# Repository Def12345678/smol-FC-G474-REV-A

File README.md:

# smol-FC

**Work in progress.** This is a Betaflight-based flight controller project, currently in the hardware design phase. 
Everything can change, it's not a final product. 

## License
This project is licensed under the **CERN Open Hardware Licence v2 - Weakly Reciprocal (CERN-OHL-W-v2)**.

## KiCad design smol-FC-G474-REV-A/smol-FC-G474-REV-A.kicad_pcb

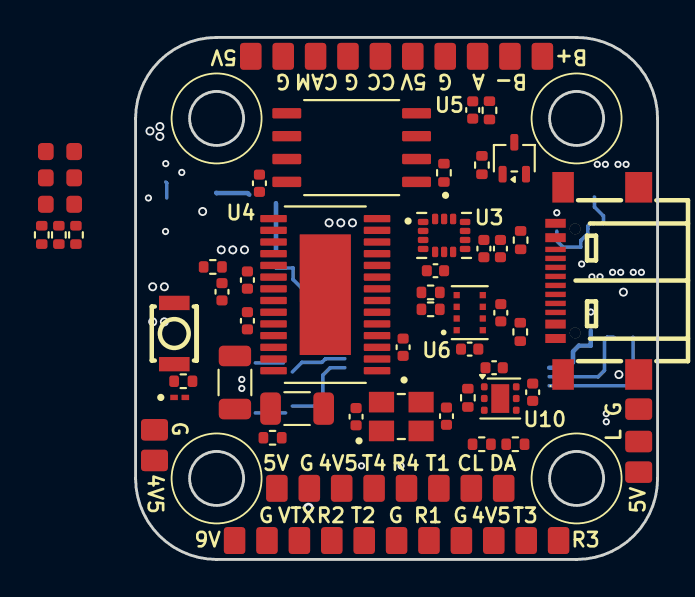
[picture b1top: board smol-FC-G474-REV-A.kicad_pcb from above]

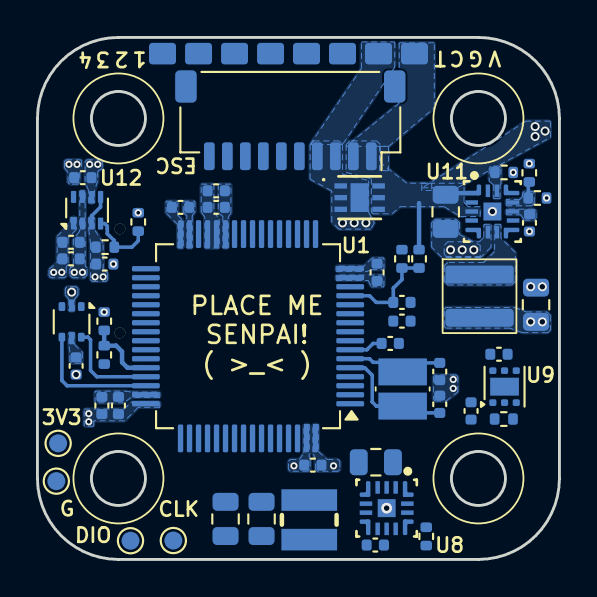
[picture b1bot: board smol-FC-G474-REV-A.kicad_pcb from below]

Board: 6 copper layers, 29.0 x 29.0 mm, 140 parts (60 on the bottom side), 83 nets.

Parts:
3V3: TestPoint; TestPoint_Pad_D1.0mm
4V5, 4V5#2, 4V5#3, 5V, 5V#2, 5V#3, 5V#4, 9V: TestPoint; pad-1.2x1.5
A: TestPoint; pad-1.2x1.5
B+: TestPoint; pad-1.2x1.5
B-: TestPoint; pad-1.2x1.5
C1, C2, C3, C4, C7, C8, C9, C10, C11, C14, C15, C16, C18, C20, C25, C26, C27: 100n; C_0402_1005Metric
C5, C28: 4.7u; C_0402_1005Metric
C6, C33, C34, C36, C39: 1u; C_0402_1005Metric
C12, C13, C23, C24: 10p; C_0402_1005Metric
C17: 2.2u; C_0402_1005Metric
C19: 10n; C_0402_1005Metric
C21, C22: 47u; C_1206_3216Metric
C29, C37: 3.3u; C_0805_2012Metric
C30, C31: 47u; C_0805_2012Metric
C32, C35, C40, C41, C42, C43: 10u; C_0402_1005Metric
C38: 22u; C_0805_2012Metric
CAM: TestPoint; pad-1.2x1.5
CC: TestPoint; pad-1.2x1.5
CL: TestPoint; pad-1.2x1.5
CLK: TestPoint; TestPoint_Pad_D1.0mm
CURR1: TestPoint; pad-1.2x1.5
D1, D2: LED; LED_0603_1608Metric
D3: ESD; DIODE_ESDALC6V1-1U2
D4: RED; LED_0603_1608Metric
DA: TestPoint; pad-1.2x1.5
DIO: TestPoint; TestPoint_Pad_D1.0mm
ESC: ESC; JST_SH_SM10B-SRSS-TB_1x10-1MP_P1.00mm_Horizontal
G: TestPoint; pad-1.2x1.5
G#2, G#3, G#4, G#5, G#6, G#7, G#8, G#9: TestPoint; pad-1.2x1.5
G#10: TestPoint; TestPoint_Pad_D1.0mm
GND4: TestPoint; pad-1.2x1.5
L: TestPoint; pad-1.2x1.5
L1: 1.5u; IND-SMD_L3.0-W3.0_YSMC0320H
L2: 3.3u; APH0430C-3R3M-TCD5
M1, M2, M3, M4: TestPoint; pad-1.2x1.5
Q1: BC817W; SOT-323_SC-70
R1, R2, R8, R19: 1k; R_0402_1005Metric
R1#2, R2#2, R3, R4: TestPoint; pad-1.2x1.5
R3#2, R6, R7, R25: 100k; R_0402_1005Metric
R4#2, R5, R20, R22, R24, R26: 10k; R_0402_1005Metric
R9, R10: 5.1k; R_0402_1005Metric
R11, R12: 75; R_0402_1005Metric
R13: 10K; R_0402_1005Metric
R14, R15, R17, R18: 4.7k; R_0402_1005Metric
R16: 330; R_0402_1005Metric
R21: 7.15k; R_0402_1005Metric
R23: 80.6k; R_0402_1005Metric
R27: 39k; R_0402_1005Metric
SW1: BOOT; KEY-SMD_B3U-1000PM
T1, T2, T3, T4: TestPoint; pad-1.2x1.5
TEL1: TestPoint; pad-1.2x1.5
U1: STM32G474RETx; LQFP-64_10x10mm_P0.5mm
U2: USBLC6-2P6; SOT-666
U3: ICM-42688-P; PQFN50P300X250X97-14N
U4: AT7456E; SOP65P637X110-28N
U5: W25Q128JVSIQ; SOIC127P790X216-8N
U6: DPS368XTSA1; XDCR_DPS368XTSA1
U7: TVS3300DRVR; DRV6_1X1P6_TEX
U8, U11: LMQ66430R5RXBR; RXB0014A-MFG
U9, U10: LP5912-3.3DRV; WSON-6-1EP_2x2mm_P0.65mm_EP1x1.6mm
U12: TPS2116DRL; SOT-583-8
USB1: TYPE-C 16P QTWT; USB-TYPE-C-SMD_TYPE-C-16P-QTWT
VBAT1: TestPoint; pad-1.2x1.5
VTX: TestPoint; pad-1.2x1.5
Y1: 8MHz; XTAL_NX3225GD-8MHZ-STD-CRA-3
Y2: 27MHz; XTAL_TSX-3225_16.0000MF18X-AC3

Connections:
+3V3_CORE: 3V3.1 (1_1), C1.1, C2.1, C3.1, C4.1, C5.1, C6.1, C7.1, C25.1, C33.1, R1.1, R2.1, R8.1, R13.1, R17.1, R18.1, R20.1, SW1.2, U1.1 (VBAT), U1.16 (VDD), U1.28 (VREF+), U1.29 (VDDA), U1.32 (VDD), U1.48 (VDD), U1.64 (VDD), U5.3 (/WP(IO2)), U5.7 (/HOLD/RESET(IO3)), U5.8 (VCC), U9.1 (OUT)
+3V3_SENS: C17.1, C18.1, C19.1, C26.1, C27.1, C36.1, R14.1, R15.1, R22.1, U3.5 (VDDIO), U3.8 (VDD), U6.6 (VDDIO), U6.8 (VDD), U10.1 (OUT)
+5V_BEC: 5V.1 (1_1), 5V#2.1 (1_1), 5V#3.1 (1_1), 5V#4.1 (1_1), C30.1, C31.1, C42.1, L1.2, R25.1, U8.11 (VOUT_FB), U12.3 (VIN1), U12.5 (MODE)
+5V_SYS: 4V5.1 (1_1), 4V5#2.1 (1_1), 4V5#3.1 (1_1), B+.1 (1_1), C14.1, C15.1, C16.1, C32.1, C35.1, C40.1, C41.1, U4.3 (DVDD), U4.19 (~RESET), U4.21 (AVDD), U4.24 (PVDD), U9.4 (EN), U9.6 (IN), U10.4 (EN), U10.6 (IN), U12.2 (VOUT), U12.7 (VOUT)
+9V_BEC: 9V.1 (1_1), C38.1, L2.2, R23.1
+VBAT: C29.1, C37.1, ESC.1, ESC.2, R3#2.1, U7.4 (IN), U7.5 (IN), U7.6 (IN), U8.1 (EN), U8.3 (VIN), U11.1 (EN), U11.3 (VIN), VBAT1.1 (1_1)
+VBUS: C11.1, C43.1, R6.1, U2.5 (VBUS), U12.6 (VIN2), USB1.A4 (VBUS), USB1.A9 (VBUS)
/Connectors/AUX: A.1 (1_1), U1.26 (PB2)
/Connectors/BZ-: B-.1 (1_1), Q1.3 (C)
/Connectors/BZ_G: Q1.1 (B), R19.2
/Connectors/Buzzer: R19.1, U1.43 (PA9)
/Connectors/CC: R16.1, U1.62 (PB9)
/Connectors/CC_P: C28.1, CC.1 (1_1), R16.2
/Connectors/I2C3_SCL: CL.1 (1_1), R17.2, U1.42 (PA8)
/Connectors/I2C3_SDA: DA.1 (1_1), R18.2, U1.41 (PC9)
/Connectors/LED: L.1 (1_1), U1.25 (PB1)
/Connectors/M1: ESC.7, M1.1 (1_1), U1.8 (PC0)
/Connectors/M2: ESC.8, M2.1 (1_1), U1.9 (PC1)
/Connectors/M3: ESC.9, M3.1 (1_1), U1.10 (PC2)
/Connectors/M4: ESC.10, M4.1 (1_1), U1.11 (PC3)
/Connectors/RX1: R1#2.1 (1_1), U1.60 (PB7)
/Connectors/RX2 (VTX): R2#2.1 (1_1), U1.17 (PA3)
/Connectors/RX3 (ELRS): R3.1 (1_1), U1.33 (PB11)
/Connectors/RX4 (GPS): R4.1 (1_1), U1.53 (PC11)
/Connectors/RX5 (TEL): ESC.6, TEL1.1 (1_1), U1.55 (PD2)
/Connectors/TX1: T1.1 (1_1), U1.59 (PB6)
/Connectors/TX2 (VTX): T2.1 (1_1), U1.14 (PA2)
/Connectors/TX3 (ELRS): T3.1 (1_1), U1.30 (PB10)
/Connectors/TX4 (GPS): T4.1 (1_1), U1.52 (PC10)
/Connectors/VIDEO_IN: C20.1, CAM.1 (1_1), R11.1
/Connectors/VIDEO_OUT: R12.2, VTX.1 (1_1)
/MCU/ADC_CURR: C10.1, CURR1.1 (1_1), ESC.5, U1.12 (PA0)
/MCU/ADC_VBAT: C9.1, R3#2.2, R4#2.1, U1.13 (PA1)
/MCU/BOOT: D3.1, R5.1, SW1.1, U1.61 (PB8)
/MCU/HSE_IN: C12.1, U1.5 (PF0), Y1.1
/MCU/HSE_OUT: C13.1, U1.6 (PF1), Y1.2
/MCU/I2C4_SCL (BARO): R15.2, U1.38 (PC6), U6.4 (SCK)
/MCU/I2C4_SDA (BARO): R14.2, U1.39 (PC7), U6.3 (SDI)
/MCU/IMU_IRQ: U1.40 (PC8), U3.4 (INT1/INT)
/MCU/LED_B: D1.1 (K), U1.24 (PB0)
/MCU/LED_B_R: D1.2 (A), R1.2
/MCU/LED_G: D2.1 (K), U1.23 (PC5)
/MCU/LED_G_R: D2.2 (A), R2.2
/MCU/LED_PWR: D4.2 (A), R8.2
/MCU/MCU_USB_D_N: U1.45 (PA11), U2.6 (I/O1)
/MCU/MCU_USB_D_P: U1.46 (PA12), U2.4 (I/O2)
/MCU/NRST: C8.1, U1.7 (PG10)
/MCU/SPI1_CS (OSD): U1.18 (PA4), U4.8 (~CS)
/MCU/SPI1_MISO (OSD): U1.20 (PA6), U4.11 (SDOUT)
/MCU/SPI1_MOSI (OSD): U1.21 (PA7), U4.9 (SDIN)
/MCU/SPI1_SCK (OSD): U1.19 (PA5), U4.10 (SCLK)
/MCU/SPI2_CS (IMU): U1.34 (PB12), U3.12 (AP_CS)
/MCU/SPI2_MISO (IMU): U1.36 (PB14), U3.1 (AP_SDO/AP_AD0)
/MCU/SPI2_MOSI (IMU): U1.37 (PB15), U3.14 (AP_SDA/AP_SDIO/AP_SDI)
/MCU/SPI2_SCK (IMU): U1.35 (PB13), U3.13 (AP_SCL/AP_SCLK)
/MCU/SPI3_CS (Blackbox): R13.2, U1.51 (PA15), U5.1 (/CS)
/MCU/SPI3_MISO (Blackbox): U1.57 (PB4), U5.2 (DO(IO1))
/MCU/SPI3_MOSI (Blackbox): U1.58 (PB5), U5.5 (DI(IO0))
/MCU/SPI3_SCK (Blackbox): U1.56 (PB3), U5.6 (CLK)
/MCU/SWCLK: CLK.1 (1_1), U1.50 (PA14)
/MCU/SWDIO: DIO.1 (1_1), U1.49 (PA13)
/MCU/USB_CC1: R10.1, USB1.B5 (CC2)
/MCU/USB_CC2: R9.1, USB1.A5 (CC1)
/MCU/USB_D_N: U2.1 (I/O1), USB1.A7 (DN1), USB1.B7 (DN2)
/MCU/USB_D_P: U2.3 (I/O2), USB1.A6 (DP1), USB1.B6 (DP2)
/MCU/USB_SENS: R6.2, R7.1, U1.44 (PA10)
/Power Supply/Buck-5V_RT: R21.1, U8.13 (RT)
/Power Supply/Buck-5V_SW: L1.1, U8.7 (SW)
/Power Supply/Buck-5V_VCC_INT: C34.1, U8.10 (VCC)
/Power Supply/Buck-9V_FB: R23.2, R24.1, U11.11 (VOUT_FB)
/Power Supply/Buck-9V_RT: R26.1, U11.13 (RT)
/Power Supply/Buck-9V_SW: L2.1, U11.7 (SW)
/Power Supply/Buck-9V_VCC_INT: C39.1, U11.10 (VCC)
/Power Supply/LDO-C_PG: R20.2, U9.3 (PG)
/Power Supply/LDO-S_PG: R22.2, U10.3 (PG)
/Power Supply/MUX_PR1: R25.2, R27.1, U12.4 (PR1)
/Sensors & IC's/OSD_CLKIN: C23.1, U4.5 (CLKIN), Y2.1
/Sensors & IC's/OSD_SAG: C22.1, U4.25 (SAG)
/Sensors & IC's/OSD_VIN: C20.2, U4.22 (VIN)
/Sensors & IC's/OSD_VOUT: C21.1, U4.26 (VOUT)
/Sensors & IC's/OSD_XFB: C24.1, U4.6 (XFB), Y2.3
/Sensors & IC's/V_OUT: C21.2, C22.2, R12.1
GND: C1.2, C2.2, C3.2, C4.2, C5.2, C6.2, C7.2, C8.2, C9.2, C10.2, C11.2, C12.2, C13.2, C14.2, C15.2, C16.2, C17.2, C18.2, C19.2, C23.2, C24.2, C25.2, C26.2, C27.2, C28.2, C29.2, C30.2, C31.2, C32.2, C33.2, C34.2, C35.2, C36.2, C37.2, C38.2, C39.2, C40.2, C41.2, C42.2, C43.2, D3.2, D4.1 (K), ESC.3, ESC.4, G.1 (1_1), G#2.1 (1_1), G#3.1 (1_1), G#4.1 (1_1), G#5.1 (1_1), G#6.1 (1_1), G#7.1 (1_1), G#8.1 (1_1), G#9.1 (1_1), G#10.1 (1_1), GND4.1 (1_1), Q1.2 (E), R4#2.2, R5.2, R7.2, R9.2, R10.2, R11.2, R21.2, R24.2, R26.2, R27.2, U1.15 (VSS), U1.27 (VSSA), U1.31 (VSS), U1.47 (VSS), U1.63 (VSS), U2.2 (GND), U3.6 (GND), U3.7 (RESV_7), U3.9 (INT2/FSYNC/CLKIN), U3.11 (RESV_11), U4.4 (DGND), U4.20 (AGND), U4.23 (PGND), U5.4 (GND), U6.1 (GND), U6.7 (GND), U7.1 (GND), U7.2 (GND), U7.3 (GND), U7.7 (EPAD), U8.6 (PGND), U8.15 (GND_DAP), U9.5 (GND), U9.7 (EP), U10.5 (GND), U10.7 (EP), U11.6 (PGND), U11.15 (GND_DAP), U12.1 (GND), USB1.0 (EH), USB1.A1 (GND), USB1.A12 (GND), Y2.2 (G), Y2.4 (G)

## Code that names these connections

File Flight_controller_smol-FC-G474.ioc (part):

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Mcu.Name=STM32G474R(B-C-E)Tx
Mcu.Package=LQFP64
Mcu.UserName=STM32G474RETx
PA0.GPIOParameters=GPIO_Label
PA0.GPIO_Label=CURR
PA0.Mode=IN1-Single-Ended
PA0.Signal=ADC1_IN1
PA1.GPIOParameters=GPIO_Label
PA1.GPIO_Label=VBAT
PA1.Mode=IN2-Single-Ended
PA1.Signal=ADC1_IN2
PA10.GPIOParameters=GPIO_Label
PA10.GPIO_Label=USD_DETECT
PA10.Signal=GPIO_Input
PA11.Mode=Device
PA11.Signal=USB_DM
PA12.Mode=Device
PA12.Signal=USB_DP
PA13.GPIOParameters=GPIO_Label
PA13.GPIO_Label=SWDIO
PA13.Mode=Serial_Wire
PA13.Signal=SYS_JTMS-SWDIO
PA14.GPIOParameters=GPIO_Label
PA14.GPIO_Label=SWCLK
PA14.Mode=Serial_Wire
PA14.Signal=SYS_JTCK-SWCLK
PA15.GPIOParameters=GPIO_Label
PA15.GPIO_Label=BLACKBOX_CS (SPI3)
PA15.Mode=NSS_Signal_Hard_Output
PA15.Signal=SPI3_NSS
PA2.GPIOParameters=GPIO_Label
PA2.GPIO_Label=VTX_TX (UART2)
PA2.Mode=Asynchronous
PA2.Signal=USART2_TX
PA3.GPIOParameters=GPIO_Label
PA3.GPIO_Label=VTX_RX (UART2)
PA3.Mode=Asynchronous
PA3.Signal=USART2_RX
PA4.GPIOParameters=GPIO_Label
PA4.GPIO_Label=OSD_CS
PA4.Mode=NSS_Signal_Hard_Output
PA4.Signal=SPI1_NSS
PA5.GPIOParameters=GPIO_Label
PA5.GPIO_Label=OSD_SCK (SPI1)
PA5.Mode=Full_Duplex_Master
PA5.Signal=SPI1_SCK
PA6.GPIOParameters=GPIO_Label
PA6.GPIO_Label=OSD_MISO (SPI1)
PA6.Mode=Full_Duplex_Master
PA6.Signal=SPI1_MISO
PA7.GPIOParameters=GPIO_Label
PA7.GPIO_Label=OSD_MOSI (SPI1)
PA7.Mode=Full_Duplex_Master
PA7.Signal=SPI1_MOSI
PA8.GPIOParameters=GPIO_Label
PA8.GPIO_Label=EXTRA_SCL (I2C3)
PA8.Mode=I2C
PA8.Signal=I2C3_SCL
PA9.GPIOParameters=GPIO_Label
PA9.GPIO_Label=Buzzer
PA9.Signal=GPIO_Output
PB0.GPIOParameters=GPIO_Label
PB0.GPIO_Label=LED_BLUE
PB0.Signal=GPIO_Output
PB1.GPIOParameters=GPIO_Label
PB1.GPIO_Label=LED (TIM3_CH4)
PB1.Signal=S_TIM3_CH4
PB10.GPIOParameters=GPIO_Label
PB10.GPIO_Label=ELRS_TX (UART3)
PB10.Mode=Asynchronous
PB10.Signal=USART3_TX
PB11.GPIOParameters=GPIO_Label
PB11.GPIO_Label=ELRS_RX (UART3)
PB11.Mode=Asynchronous
PB11.Signal=USART3_RX
PB12.GPIOParameters=GPIO_Label
PB12.GPIO_Label=IMU_CS (SPI2)
PB12.Mode=NSS_Signal_Hard_Output
PB12.Signal=SPI2_NSS
PB13.GPIOParameters=GPIO_Label
PB13.GPIO_Label=IMU_SCK (SPI2)
PB13.Mode=Full_Duplex_Master
PB13.Signal=SPI2_SCK
PB14.GPIOParameters=GPIO_Label
PB14.GPIO_Label=IMU_MISO (SPI2)
PB14.Mode=Full_Duplex_Master
PB14.Signal=SPI2_MISO
PB15.GPIOParameters=GPIO_Label
PB15.GPIO_Label=IMU_MOSI (SPI2)
PB15.Mode=Full_Duplex_Master
PB15.Signal=SPI2_MOSI
PB2.GPIOParameters=GPIO_Label
PB2.GPIO_Label=EXTRA_AUX
PB2.Signal=GPIO_Output
PB3.GPIOParameters=GPIO_Label
PB3.GPIO_Label=BLACKBOX_SCK (SPI3)
PB3.Mode=Full_Duplex_Master
PB3.Signal=SPI3_SCK
PB4.GPIOParameters=GPIO_Label
PB4.GPIO_Label=BLACKBOX_MISO (SPI3)
PB4.Mode=Full_Duplex_Master
PB4.Signal=SPI3_MISO
PB5.GPIOParameters=GPIO_Label
PB5.GPIO_Label=BLACKBOX_MOSI (SPI3)
PB5.Mode=Full_Duplex_Master
PB5.Signal=SPI3_MOSI
PB6.GPIOParameters=GPIO_Label
PB6.GPIO_Label=EXTRA_TX (UART1)
PB6.Mode=Asynchronous
PB6.Signal=USART1_TX
PB7.GPIOParameters=GPIO_Label
PB7.GPIO_Label=EXTRA_RX (UART1)
PB7.Mode=Asynchronous
PB7.Signal=USART1_RX
PB8-BOOT0.GPIOParameters=GPIO_Label
PB8-BOOT0.GPIO_Label=BOOT
PB8-BOOT0.Signal=GPIO_Input
PB9.GPIOParameters=GPIO_Label
PB9.GPIO_Label=CC (TIM4_CH4)
PB9.Signal=S_TIM4_CH4
PC0.GPIOParameters=GPIO_Label
PC0.GPIO_Label=M1 (TIM1_CH1)
PC0.Signal=S_TIM1_CH1
PC1.GPIOParameters=GPIO_Label
PC1.GPIO_Label=M2 (TIM1_CH2)
PC1.Signal=S_TIM1_CH2
PC10.GPIOParameters=GPIO_Label
PC10.GPIO_Label=GPS_TX (UART4)
PC10.Mode=Asynchronous
PC10.Signal=UART4_TX
PC11.GPIOParameters=GPIO_Label
PC11.GPIO_Label=GPS_RX (UART4)
PC11.Mode=Asynchronous
PC11.Signal=UART4_RX
PC12.GPIOParameters=GPIO_Label
PC12.GPIO_Label=TEL_TX (UART5)
PC12.Mode=Asynchronous
PC12.Signal=UART5_TX
PC2.GPIOParameters=GPIO_Label
PC2.GPIO_Label=M3 (TIM1_CH3)
PC2.Signal=S_TIM1_CH3
PC3.GPIOParameters=GPIO_Label
PC3.GPIO_Label=M4 (TIM1_CH4)
PC3.Signal=S_TIM1_CH4
PC4.GPIOParameters=GPIO_Label
PC4.GPIO_Label=LED_AMBER
PC4.Signal=GPIO_Output
PC5.GPIOParameters=GPIO_Label
PC5.GPIO_Label=LED_GREEN
PC5.Signal=GPIO_Output
PC6.GPIOParameters=GPIO_Label
PC6.GPIO_Label=BARO_SCL (I2C4)
PC6.Mode=I2C
PC6.Signal=I2C4_SCL
PC7.GPIOParameters=GPIO_Label
PC7.GPIO_Label=BARO_SDA (I2C4)
PC7.Mode=I2C
PC7.Signal=I2C4_SDA
PC8.GPIOParameters=GPIO_Label
PC8.GPIO_Label=IMU_IRQ
PC8.Signal=GPIO_Input
PC9.GPIOParameters=GPIO_Label
PC9.GPIO_Label=EXTRA_SDA (I2C3)
PC9.Mode=I2C
PC9.Signal=I2C3_SDA
PD2.GPIOParameters=GPIO_Label
PD2.GPIO_Label=TEL_RX (UART5)
PD2.Mode=Asynchronous
PD2.Signal=UART5_RX
PF0-OSC_IN.GPIOParameters=GPIO_Label
PF0-OSC_IN.GPIO_Label=HSE_IN
PF0-OSC_IN.Mode=HSE-External-Oscillator
PF0-OSC_IN.Signal=RCC_OSC_IN
PF1-OSC_OUT.GPIOParameters=GPIO_Label
PF1-OSC_OUT.GPIO_Label=HSE_OUT
PF1-OSC_OUT.Mode=HSE-External-Oscillator
PF1-OSC_OUT.Signal=RCC_OSC_OUT
PG10-NRST.GPIOParameters=GPIO_Label
PG10-NRST.GPIO_Label=NRST
PG10-NRST.Signal=GPIO_Input
RCC.HSE_VALUE=8000000
RCC.SYSCLKFreq_VALUE=16000000
board=custom

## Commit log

2026-05-24 added cubeMX pinout
2026-05-25 Add licensing information to README.md
2026-05-25 Added license, and started working on schematic
2026-05-25 Changed license
2026-05-26 Update README with project status and license
    Added project description and updated license information.
2026-05-26 Revise README with project description and license
    Updated README to include project details and license information.
2026-05-26 Fix formatting in README.md
2026-05-26 added USB-C section
2026-05-27 Schematic update
2026-05-29 Added whole new schematic (sensors, OSD, Blackbox), changed text in cubemx
2026-05-31 complete connectors layout and initialize buck converter section. Added buck docs in /docs.
2026-06-02 Updated Buck-5V doc, added Buck 5V/10V and LDO for 3v3 on schematic
2026-06-02 Changed 10V buck to 9V buck
2026-06-05 Attached footprints and finalized schematic.
2026-06-09 Finalized schematic, added power mux
2026-06-12 In progress PCB layout
2026-06-14 changed size of cap on buck's
2026-06-24 Opis Twoich zmian

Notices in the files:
smol-FC-G474-REV-A/smol-FC-G474-REV-A.kicad_pcb:
License: CERN-OHL-W v2
